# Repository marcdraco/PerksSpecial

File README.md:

NOTE: this is superceded by Sarah

# PerksSpecial
Custom PCB for the JLI2555 Capsule 
After long delays in my redesign of Matthew Perks’ excellent USB 3.0 microphone, I’m releasing this very simple design that will work with many TO92 and TO71 JFETs.

It’s primarily designed with the LSK170(a-c) or the LSK389 but should also work with any low-voltage JFETs designed for condenser microphone applications such as the 2K208 - which is lpower cost than it's higher-performance (lower noise) brethren. It's worth noting that even the cheapest FETs have respectably low noise for the application but it's better to check the datasheet so you don't buy something optimised for a different application. Whatever you choose, it MUST be an N-type.

ALL three (technically four) devices are wired in parallel as can be seen in the schematic, but you should only fit one appropriate to the device you have. I recommend that LSK170 which is low noise, in current production and not especially expensive.

The name tag should break right off if you want to- the silkscreen doesn't have the part numbers as there are a fair number in different packages that will also work (to some degree).

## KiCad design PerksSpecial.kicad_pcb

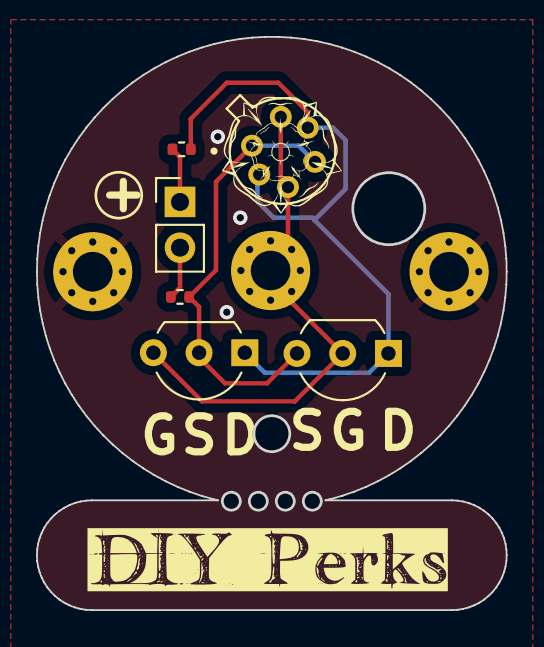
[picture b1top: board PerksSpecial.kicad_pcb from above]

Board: 2 copper layers, 26.1 x 31.8 mm, 9 parts (0 on the bottom side), 6 nets.

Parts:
G101, G102: MountingHole_2.2mm_M2_Pad_Via
J101: Conn_01x02_Pin; PinHeader_1x02_P2.54mm_Vertical
Pad101: MountingHole_2.2mm_M2_Pad_Via
Q101: LKS170; TO-92_Inline_Wide
Q102: 2SK208; TO-92L_Inline_Wide
R101, R102: 2k2; R_0402_1005Metric
U101: to71

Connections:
GNDA: G101.1, G102.1
MGate: Pad101.1, Q101.2 (G), Q102.3 (G), U101.3 (G), U101.6 (G)
unnamed: J101.1, R101.2
unnamed: J101.2, R102.1
unnamed: Q101.1 (D), Q102.1 (D), R101.1, U101.2 (D), U101.5 (D)
unnamed: Q101.3 (S), Q102.2 (S), R102.2, U101.1 (S), U101.4 (S)

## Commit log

2023-06-23 Update README.md
    Removed the two 2k2 resistors from the design for direct compatibility with Matt's original design.
